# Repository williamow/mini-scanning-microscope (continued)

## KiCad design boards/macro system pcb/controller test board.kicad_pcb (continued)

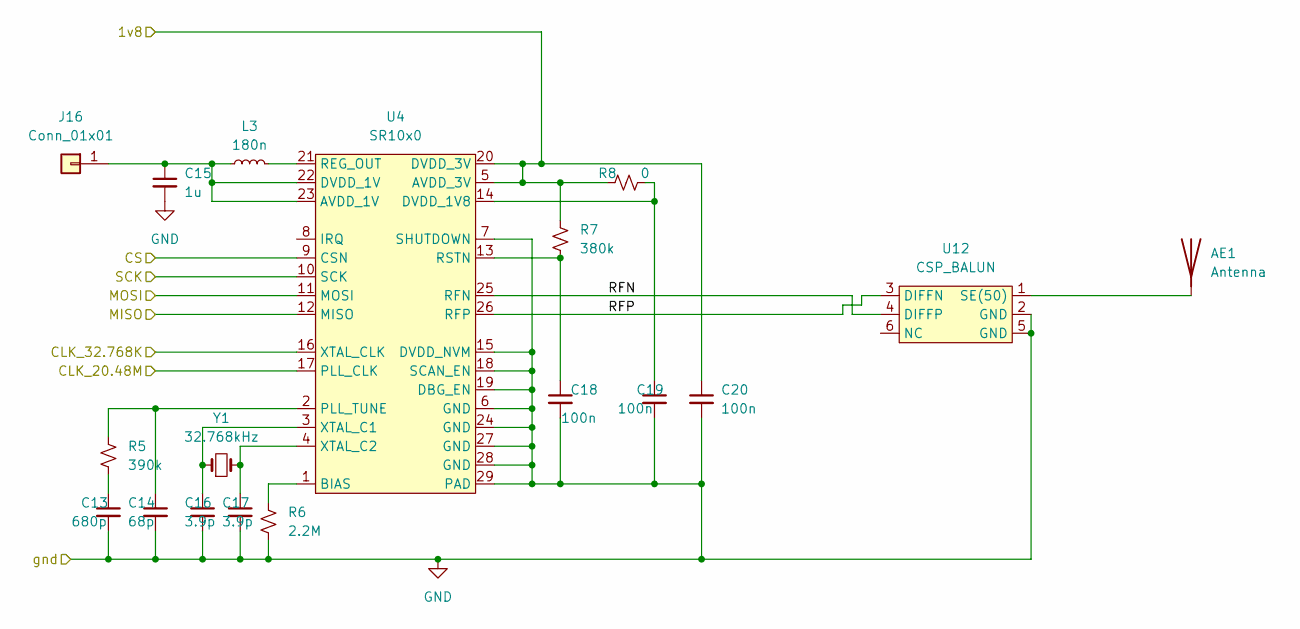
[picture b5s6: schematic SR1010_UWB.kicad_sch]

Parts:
AE1: Antenna; antenna_footprint
C13: 680p; C_0603_1608Metric_Pad1.08x0.95mm_HandSolder
C14: 68p; C_0603_1608Metric_Pad1.08x0.95mm_HandSolder
C15: 1u; C_0603_1608Metric_Pad1.08x0.95mm_HandSolder
C16, C17: 3.9p; C_0603_1608Metric_Pad1.08x0.95mm_HandSolder
C18, C19, C20: 100n; C_0603_1608Metric_Pad1.08x0.95mm_HandSolder
J16: Conn_01x01; PinHeader_1x01_P2.54mm_Vertical
L3: 180n; L_0603_1608Metric_Pad1.05x0.95mm_HandSolder
R5: 390k; R_0603_1608Metric_Pad0.98x0.95mm_HandSolder
R6: 2.2M; R_0603_1608Metric_Pad0.98x0.95mm_HandSolder
R7: 380k; R_0603_1608Metric_Pad0.98x0.95mm_HandSolder
R8: 0; R_0603_1608Metric_Pad0.98x0.95mm_HandSolder
U4: SR10x0; QFN-28-1EP_4x4mm_P0.4mm_EP2.3x2.3mm
U12: CSP_BALUN
Y1: 32.768kHz; Crystal_SMD_MicroCrystal_CM9V-T1A-2Pin_1.6x1.0mm_HandSolder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

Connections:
/ICE40UP5K/CLK_20.48M: U4.17 (PLL_CLK); also elsewhere on the board
/ICE40UP5K/CLK_32.768K: U4.16 (XTAL_CLK); also elsewhere on the board
/ICE40UP5K/UWB_CS: U4.9 (CSN); also elsewhere on the board
/ICE40UP5K/UWB_MISO: U4.12 (MISO); also elsewhere on the board
/ICE40UP5K/UWB_MOSI: U4.11 (MOSI); also elsewhere on the board
/ICE40UP5K/UWB_SCK: U4.10 (SCK); also elsewhere on the board
/SR1010_UWB/1v8: C20.1, R7.2, R8.1, U4.5 (AVDD_3V), U4.20 (DVDD_3V); also elsewhere on the board
/SR1010_UWB/RFN: U4.25 (RFN), U12.4 (DIFFP)
/SR1010_UWB/RFP: U4.26 (RFP), U12.3 (DIFFN)
GND: C13.2, C14.2, C15.2, C16.2, C17.2, C18.2, C19.2, C20.2, R6.1, U4.6 (GND), U4.7 (SHUTDOWN), U4.15 (DVDD_NVM), U4.18 (SCAN_EN), U4.19 (DBG_EN), U4.24 (GND), U4.27 (GND), U4.28 (GND), U4.29 (PAD), U12.2 (GND), U12.5 (GND); also elsewhere on the board
unnamed: C13.1, R5.1
unnamed: C14.1, R5.2, U4.2 (PLL_TUNE)
unnamed: C15.1, J16.1, L3.1, U4.22 (DVDD_1V), U4.23 (AVDD_1V)
unnamed: C16.1, U4.3 (XTAL_C1), Y1.1
unnamed: C17.1, U4.4 (XTAL_C2), Y1.2
unnamed: C18.1, R7.1, U4.13 (RSTN)
unnamed: C19.1, R8.2, U4.14 (DVDD_1V8)
unnamed: L3.2, U4.21 (REG_OUT)
unnamed: R6.2, U4.1 (BIAS)
unnamed: AE1.1 (A), U12.1 (SE(50))

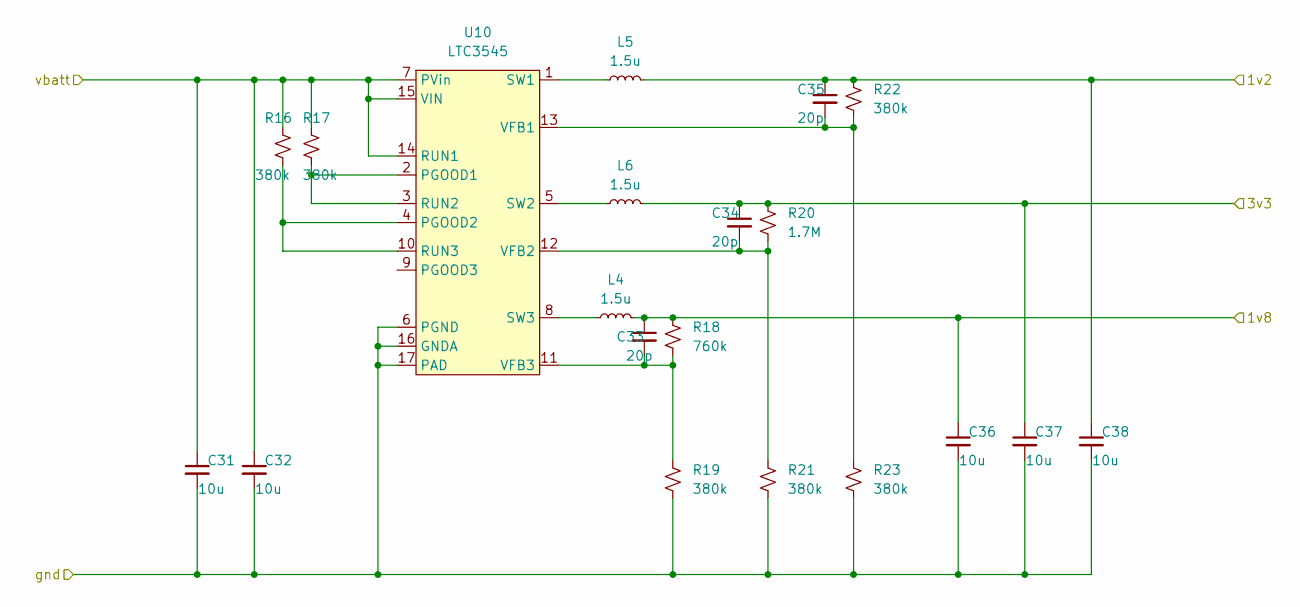
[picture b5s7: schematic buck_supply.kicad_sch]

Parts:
C31, C32, C36, C37, C38: 10u; C_0603_1608Metric_Pad1.08x0.95mm_HandSolder
C33, C34, C35: 20p; C_0603_1608Metric_Pad1.08x0.95mm_HandSolder
L4, L5, L6: 1.5u; L_0603_1608Metric_Pad1.05x0.95mm_HandSolder
R16, R17, R19, R21, R22, R23: 380k; R_0603_1608Metric_Pad0.98x0.95mm_HandSolder
R18: 760k; R_0603_1608Metric_Pad0.98x0.95mm_HandSolder
R20: 1.7M; R_0603_1608Metric_Pad0.98x0.95mm_HandSolder
U10: LTC3545; QFN-16-1EP_3x3mm_P0.5mm_EP1.45x1.45mm

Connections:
/1v2: C35.1, C38.1, L5.2, R22.2; also elsewhere on the board
/1v8: C33.1, C36.1, L4.2, R18.2; also elsewhere on the board
/3v3: C34.1, C37.1, L6.2, R20.2; also elsewhere on the board
/buck_supply/vbatt: C31.1, C32.1, R16.2, R17.2, U10.7 (PVin), U10.14 (RUN1), U10.15 (VIN); also elsewhere on the board
GND: C31.2, C32.2, C36.2, C37.2, C38.2, R19.1, R21.1, R23.1, U10.6 (PGND), U10.16 (GNDA), U10.17 (PAD); also elsewhere on the board
unnamed: C33.2, R18.1, R19.2, U10.11 (VFB3)
unnamed: C34.2, R20.1, R21.2, U10.12 (VFB2)
unnamed: C35.2, R22.1, R23.2, U10.13 (VFB1)
unnamed: L4.1, U10.8 (SW3)
unnamed: L5.1, U10.1 (SW1)
unnamed: L6.1, U10.5 (SW2)
unnamed: R16.1, U10.4 (PGOOD2), U10.10 (RUN3)
unnamed: R17.1, U10.2 (PGOOD1), U10.3 (RUN2)

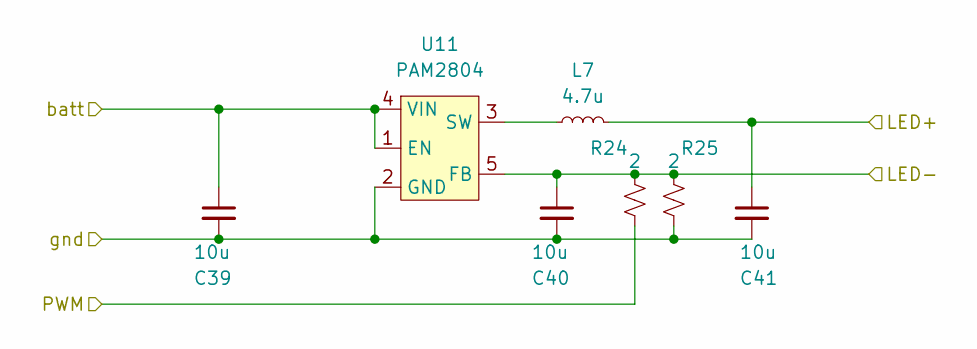
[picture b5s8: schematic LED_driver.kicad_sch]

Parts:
C39, C40, C41: 10u; C_0603_1608Metric_Pad1.08x0.95mm_HandSolder
L7: 4.7u; L_0805_2012Metric_Pad1.05x1.20mm_HandSolder
R24, R25: 2; R_0603_1608Metric_Pad0.98x0.95mm_HandSolder
U11: PAM2804; TSOT-23-5_HandSoldering

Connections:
/ICE40UP5K/LED_drive: R24.1; also elsewhere on the board
/LED_driver/LED+: C41.1, L7.2; also elsewhere on the board
/LED_driver/LED-: C40.1, R24.2, R25.2, U11.5 (FB); also elsewhere on the board
/LED_driver/batt: C39.1, U11.1 (EN), U11.4 (VIN); also elsewhere on the board
GND: C39.2, C40.2, C41.2, R25.1, U11.2 (GND); also elsewhere on the board
unnamed: L7.1, U11.3 (SW)

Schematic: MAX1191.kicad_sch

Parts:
C22: 1u; C_0603_1608Metric_Pad1.08x0.95mm_HandSolder
C23, C24, C25, C26: 100n; C_0603_1608Metric_Pad1.08x0.95mm_HandSolder
U6: MAX1191; QFN-28-1EP_5x5mm_P0.5mm_EP3.35x3.35mm

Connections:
/ICE40UP5K/ADC_A/B: U6.17 (A/Bn); also elsewhere on the board
/ICE40UP5K/ADC_CLK: U6.4 (CLK); also elsewhere on the board
/ICE40UP5K/ADC_D0: U6.21 (D0); also elsewhere on the board
/ICE40UP5K/ADC_D1: U6.20 (D1); also elsewhere on the board
/ICE40UP5K/ADC_D2: U6.19 (D2); also elsewhere on the board
/ICE40UP5K/ADC_D3: U6.18 (D3); also elsewhere on the board
/ICE40UP5K/ADC_D4: U6.16 (D4); also elsewhere on the board
/ICE40UP5K/ADC_D5: U6.15 (D5); also elsewhere on the board
/ICE40UP5K/ADC_D6: U6.14 (D6); also elsewhere on the board
/ICE40UP5K/ADC_D7: U6.13 (D7); also elsewhere on the board
/MAX1191/1v8: C22.1, U6.12 (OVDD), U6.22 (PD1), U6.23 (PD0); also elsewhere on the board
/MAX1191/3v3: C23.1, U6.8 (VDD), U6.9 (VDD), U6.28 (VDD); also elsewhere on the board
/MAX1191/Vin: U6.1 (INA-), U6.7 (INB-); also elsewhere on the board
/MAX1191/max_vref: C26.1, U6.27 (REFP); also elsewhere on the board
GND: C22.2, C23.2, C24.2, C25.2, C26.2, U6.3 (GND), U6.5 (GND), U6.10 (GND), U6.11 (OGND), U6.29 (PAD); also elsewhere on the board
unnamed: C24.1, U6.26 (REFN)
unnamed: C25.1, U6.2 (INA+), U6.6 (INB+), U6.25 (COM)

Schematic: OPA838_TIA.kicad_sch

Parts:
C27, C28: 100n; C_0603_1608Metric_Pad1.08x0.95mm_HandSolder
C45: 50p; C_0603_1608Metric_Pad1.08x0.95mm_HandSolder
J10, J14: Conn_Coaxial; SMA_Amphenol_901-144_Vertical
R9: TIA_FB; R_0603_1608Metric_Pad0.98x0.95mm_HandSolder
R41: 50; R_0603_1608Metric_Pad0.98x0.95mm_HandSolder
U7: OPA838SIDCKT; SOT-363_SC-70-6_Handsoldering

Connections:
/MAX1191/Vin: J10.1 (In), R9.2, U7.1; also elsewhere on the board
/MAX1191/max_vref: C27.1, R41.2, U7.3 (+); also elsewhere on the board
/TIA/3v3: C28.1, U7.5 (~DISABLE), U7.6 (V+); also elsewhere on the board
/TIA/I_APD: C45.2, J14.1 (In), R9.1, U7.4 (-); also elsewhere on the board
GND: C27.2, C28.2, J10.2 (Ext), J14.2 (Ext), U7.2 (V-); also elsewhere on the board
unnamed: C45.1, R41.1

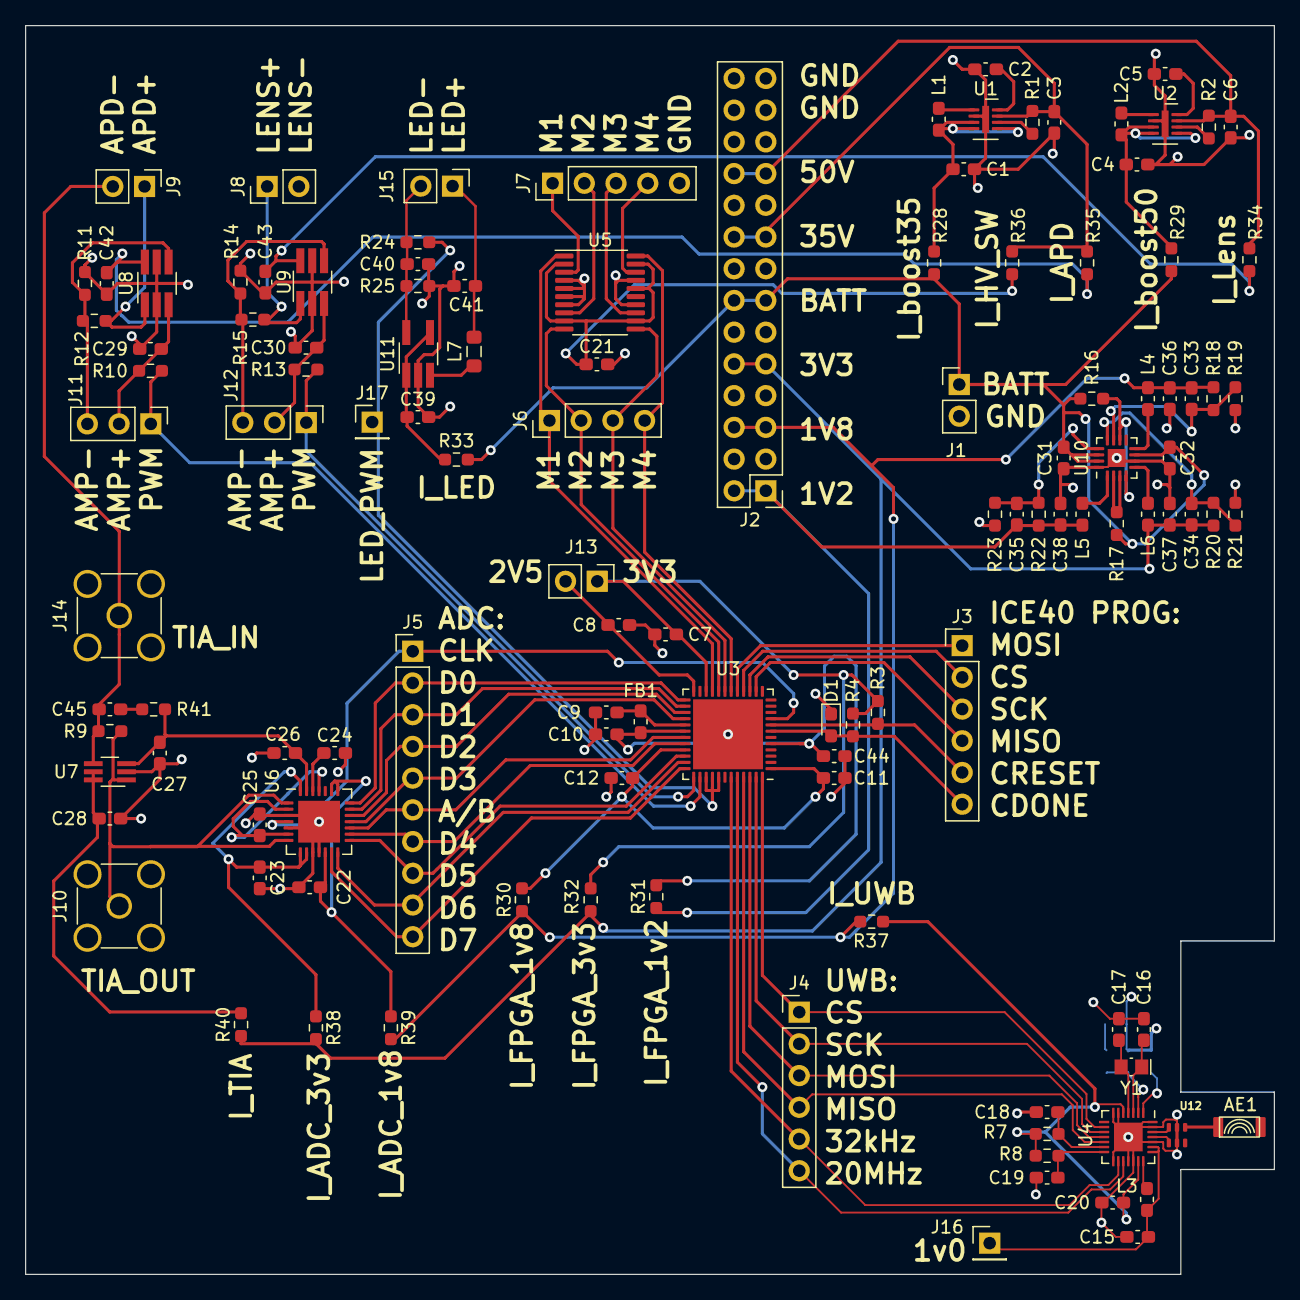
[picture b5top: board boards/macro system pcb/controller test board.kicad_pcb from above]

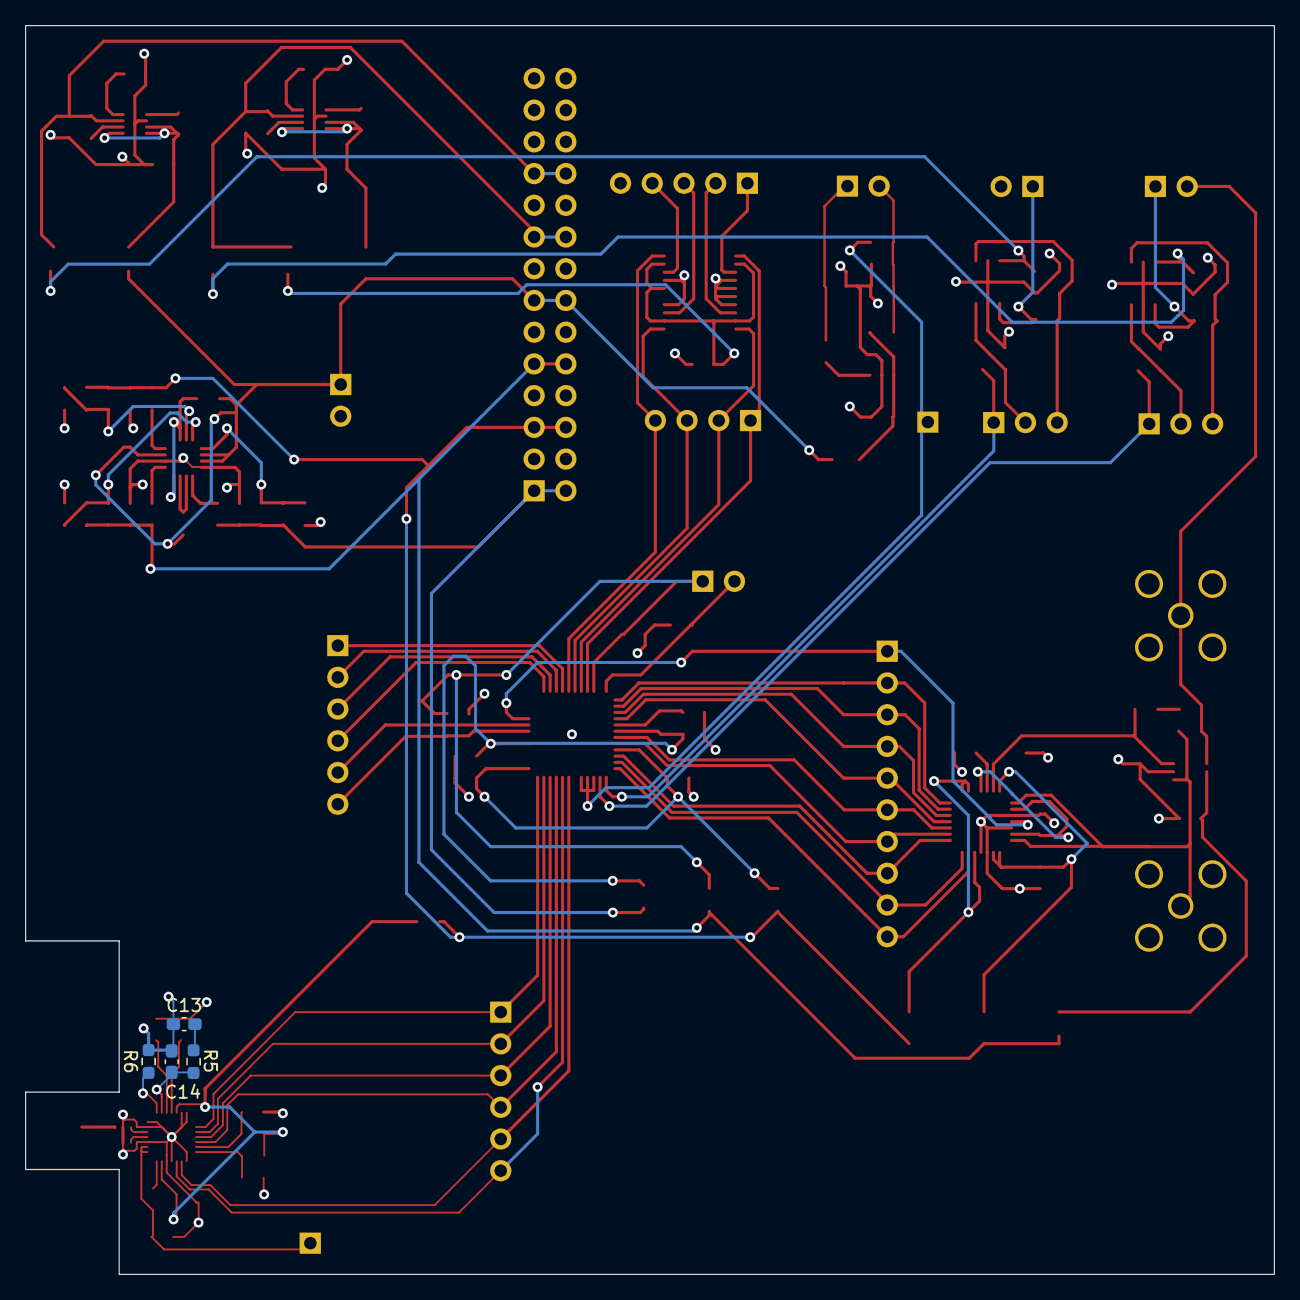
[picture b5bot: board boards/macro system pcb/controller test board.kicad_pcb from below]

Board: 4 copper layers, 100.0 x 100.0 mm, 124 parts (4 on the bottom side), 96 nets.

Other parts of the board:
C4, C6: 1u; C_0603_1608Metric_Pad1.08x0.95mm_HandSolder
C5: 0.22u; C_0603_1608Metric_Pad1.08x0.95mm_HandSolder
C29, C42: 100n; C_0603_1608Metric_Pad1.08x0.95mm_HandSolder
J11: Conn_01x03; PinHeader_1x03_P2.54mm_Vertical
L2: 15u; L_0603_1608Metric_Pad1.05x0.95mm_HandSolder
R10, R11: 100k; R_0603_1608Metric_Pad0.98x0.95mm_HandSolder
R12: 3M; R_0603_1608Metric_Pad0.98x0.95mm_HandSolder
U2: LT3494; DFN-8-1EP_2x3mm_P0.5mm_EP0.56x2.15mm
U8: ADA4097; TSOT-23-6_HandSoldering

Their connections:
/50v: C6.1, U2.7 (VOUT); also elsewhere on the board
/HVbias/HV_bias: R12.2, U8.1; also elsewhere on the board
/HVbias/PWM_in: J11.1, R10.1; also elsewhere on the board
/HVbias/VHV: C42.1, U8.6 (V+); also elsewhere on the board
/LT3494_boost1/FB: U2.6 (FB); also elsewhere on the board
/LT3494_boost1/Vbatt: C4.1, L2.1, U2.3 (VCC), U2.4 (CTRL), U2.5 (EN); also elsewhere on the board
GND: C4.2, C5.2, C6.2, C29.2, C42.2, R11.1, U2.2 (GND), U2.9 (PAD), U8.2 (V-), U8.5 (~DISABLE); also elsewhere on the board
unnamed: C5.1, U2.8 (CAP)
unnamed: C29.1, J11.2, R10.2, U8.3 (+)
unnamed: J11.3, R11.2, R12.1, U8.4 (-)
unnamed: L2.2, U2.1 (SW)

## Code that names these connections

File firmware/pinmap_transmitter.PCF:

# ##############################################################################
# iCEcube PCF
# Version:            2012.09SP1.22498
# File Generated:     Sep 14 2013 17:36:59
# Family & Device:    iCE40UP5K
# Package:            SG48

# ##############################################################################
# apparently pin 35 input conflicts with having a PLL in the design

set_io -nowarn UWB_CS   48
set_io -nowarn UWB_MISO 45
set_io -nowarn UWB_MOSI 46
set_io -nowarn UWB_SCK  47

set_io -nowarn FTDI_cfg_cs   16
set_io -nowarn FTDI_miso     14
set_io -nowarn FTDI_mosi     17
set_io -nowarn FTDI_sck      15

set_io -nowarn Xp		18
set_io -nowarn Xn		19
set_io -nowarn Yp		20
set_io -nowarn Yn		21

set_io -nowarn ADC_data[0] 25
set_io -nowarn ADC_data[1] 26
set_io -nowarn ADC_data[2] 27
set_io -nowarn ADC_data[3] 28
set_io -nowarn ADC_data[4] 32
set_io -nowarn ADC_data[5] 34
set_io -nowarn ADC_data[6] 31 #re-route using the A/B pin
set_io -nowarn ADC_data[7] 36
set_io -nowarn ADC_clk 9

set_io -nowarn APD_pwm 38

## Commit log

2024-07-01 organized existing design files into a more organized structure
2024-10-22 made macro system pcb v2
2025-01-30 create new LD only mount PCB
2025-09-03 updated physical scanning chassis
2025-09-03 stopped tracking old optics designs
